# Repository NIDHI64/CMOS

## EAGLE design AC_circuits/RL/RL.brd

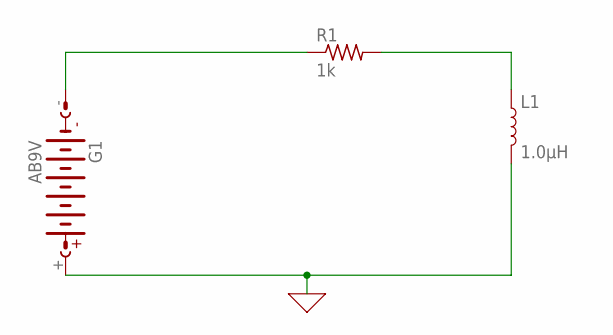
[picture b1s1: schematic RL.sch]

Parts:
G1: AB9V
L1: 1.0μH; 0805-WIDE
R1: 1k; 0204V

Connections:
0: G1.+, L1.2
unnamed: G1.-, R1.1
unnamed: L1.1, R1.2

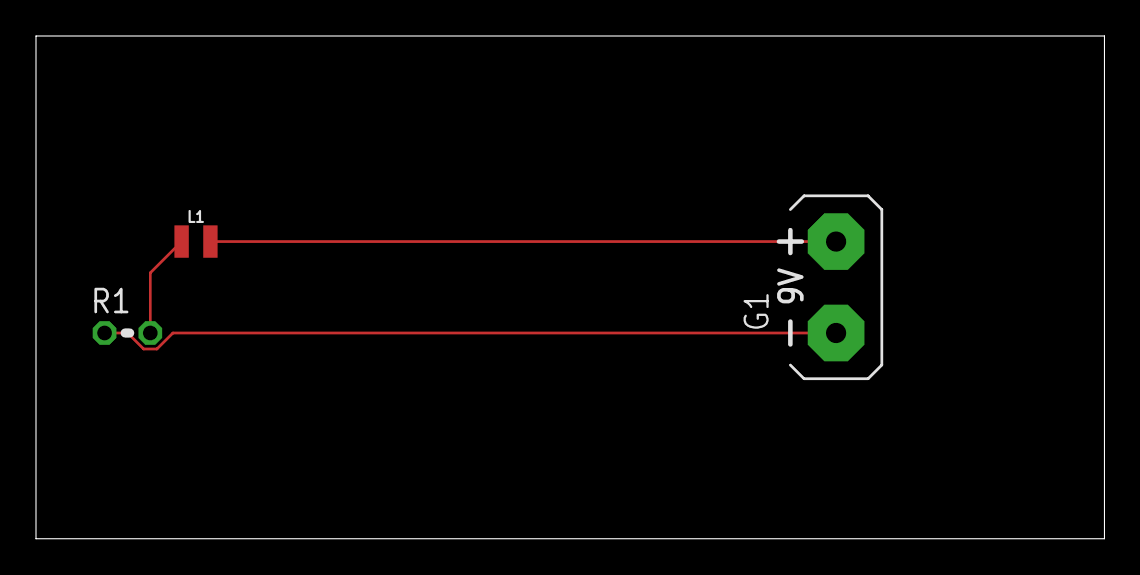
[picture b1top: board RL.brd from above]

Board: 2 copper layers, 59.4 x 27.9 mm, 3 parts (0 on the bottom side), 3 nets.

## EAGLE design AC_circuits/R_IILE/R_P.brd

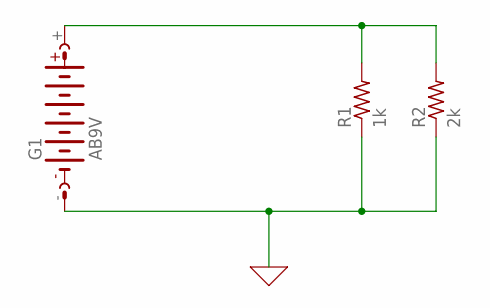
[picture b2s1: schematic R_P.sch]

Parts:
G1: AB9V
R1: 1k; 0204V
R2: 2k; 0204V

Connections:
0: G1.-, R1.1, R2.1
unnamed: G1.+, R1.2, R2.2

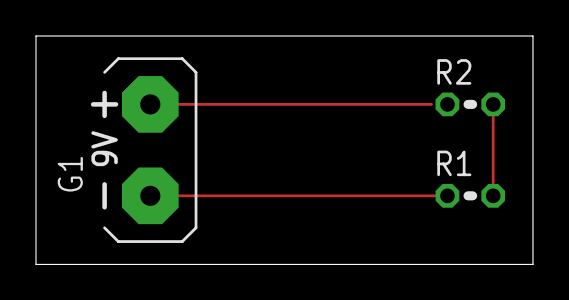
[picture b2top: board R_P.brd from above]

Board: 2 copper layers, 27.6 x 12.7 mm, 3 parts (0 on the bottom side), 2 nets.

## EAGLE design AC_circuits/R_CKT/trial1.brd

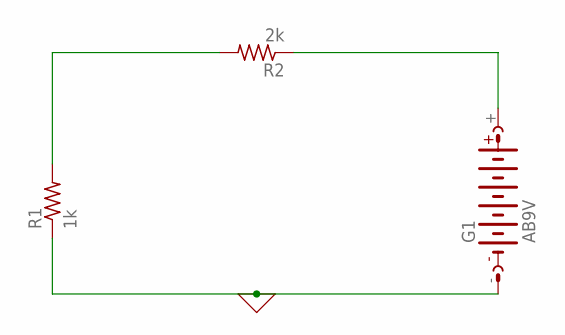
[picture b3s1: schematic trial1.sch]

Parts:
G1: AB9V
R1: 1k; 0204V
R2: 2k; 0204V

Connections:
0: G1.-, R1.1
unnamed: R1.2, R2.2
unnamed: G1.+, R2.1

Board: 2 copper layers, 3 parts (0 on the bottom side), 3 nets, no tracks yet.

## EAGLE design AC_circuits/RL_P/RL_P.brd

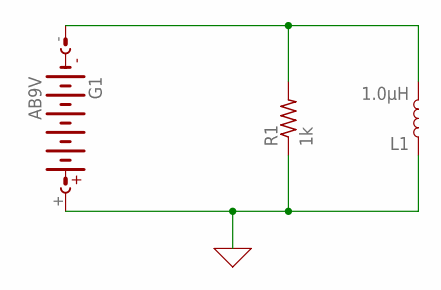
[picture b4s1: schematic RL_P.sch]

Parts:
G1: AB9V
L1: 1.0μH; 0805-WIDE
R1: 1k; 0204V

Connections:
0: G1.+, L1.1, R1.1
unnamed: G1.-, L1.2, R1.2

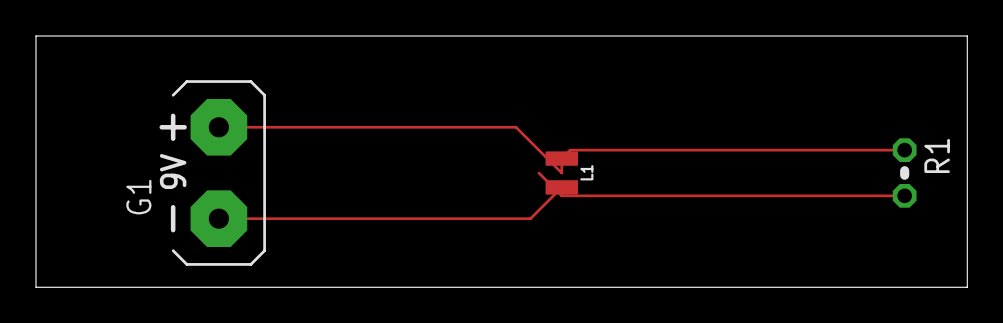
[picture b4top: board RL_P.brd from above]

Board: 2 copper layers, 51.7 x 14.0 mm, 3 parts (0 on the bottom side), 2 nets.

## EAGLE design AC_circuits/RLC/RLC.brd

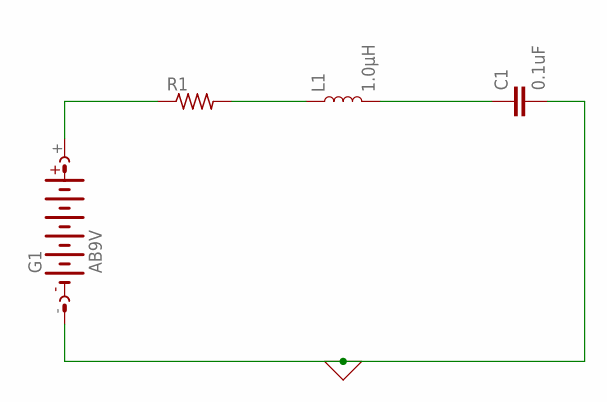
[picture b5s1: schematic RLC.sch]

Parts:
C1: 0.1uF; 0402
G1: AB9V
L1: 1.0μH; 0805-WIDE
R1: R-US_0204/2V; 0204V

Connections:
0: C1.2, G1.-
unnamed: G1.+, R1.1
unnamed: L1.1, R1.2
unnamed: C1.1, L1.2

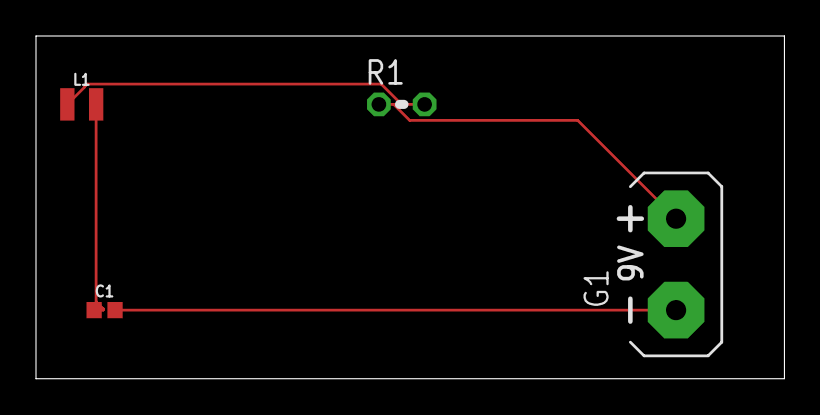
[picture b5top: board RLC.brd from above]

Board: 2 copper layers, 41.6 x 19.0 mm, 4 parts (0 on the bottom side), 4 nets.

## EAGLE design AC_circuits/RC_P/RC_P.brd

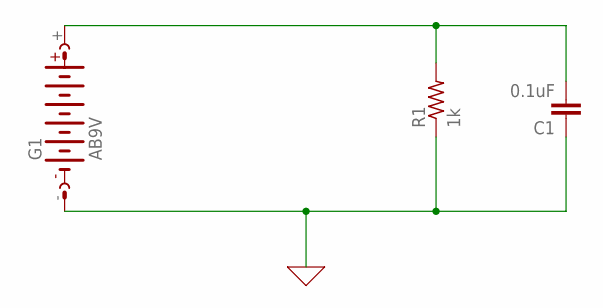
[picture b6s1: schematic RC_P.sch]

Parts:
C1: 0.1uF; 0402
G1: AB9V
R1: 1k; 0204V

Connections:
0: C1.1, G1.-, R1.1
unnamed: C1.2, G1.+, R1.2

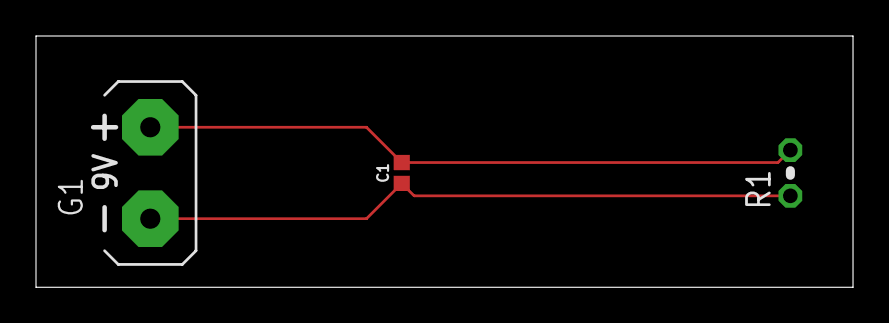
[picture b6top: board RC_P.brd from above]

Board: 2 copper layers, 45.4 x 14.0 mm, 3 parts (0 on the bottom side), 2 nets.

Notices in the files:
parts and their libraries:
SparkFun-Capacitors: Licensing: Creative Commons ShareAlike 4.0 International - https://creativecommons.org/licenses/by-sa/4.0
